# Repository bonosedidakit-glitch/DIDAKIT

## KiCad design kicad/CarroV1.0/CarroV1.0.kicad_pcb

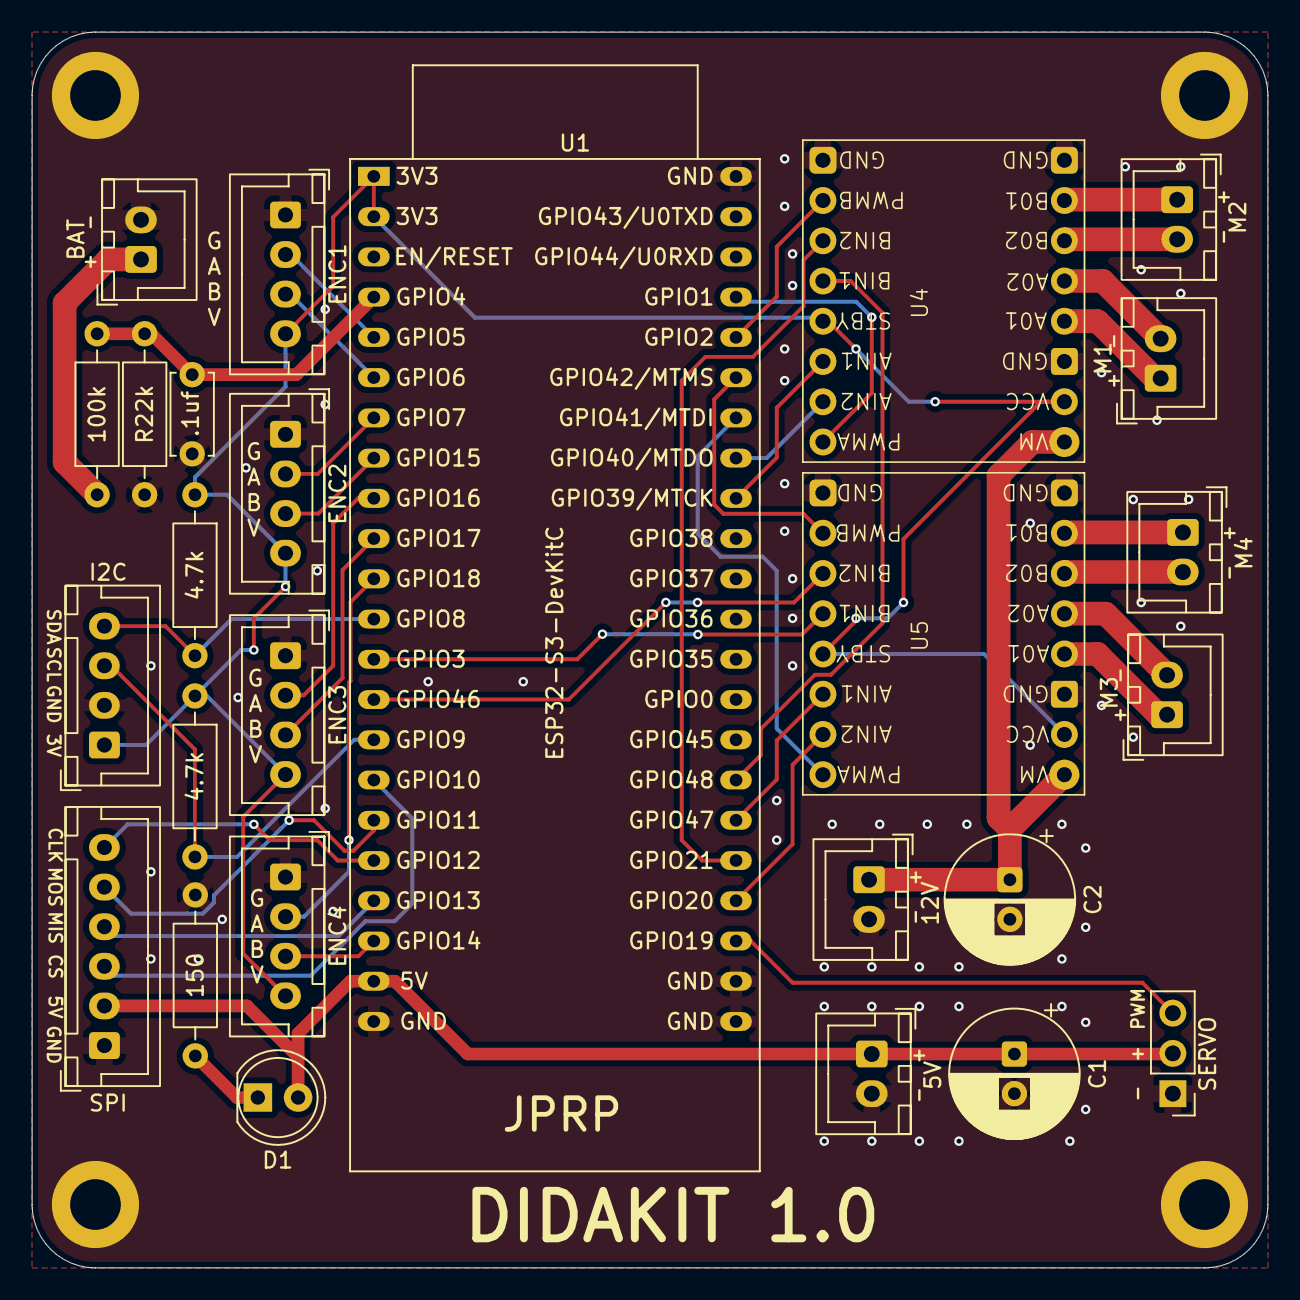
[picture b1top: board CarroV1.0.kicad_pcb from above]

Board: 2 copper layers, 78.0 x 78.0 mm, 26 parts (0 on the bottom side), 42 nets.

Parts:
4.7k: 4.7K; R_Axial_DIN0207_L6.3mm_D2.5mm_P10.16mm_Horizontal
4.7k#2: 4.7k; R_Axial_DIN0207_L6.3mm_D2.5mm_P10.16mm_Horizontal
5V: INPUT 5V; JST_XH_B2B-XH-A_1x02_P2.50mm_Vertical
12V: INPUT 12V; JST_XH_B2B-XH-A_1x02_P2.50mm_Vertical
100k: 100k; R_Axial_DIN0207_L6.3mm_D2.5mm_P10.16mm_Horizontal
150: 150; R_Axial_DIN0207_L6.3mm_D2.5mm_P10.16mm_Horizontal
.1uf: 100nF; C_Disc_D5.0mm_W2.5mm_P5.00mm
BAT: INPUT_battery; JST_XH_B2B-XH-A_1x02_P2.50mm_Vertical
C1, C2: 1000uF; CP_Radial_D8.0mm_P2.50mm
D1: LED; LED_D5.0mm
ENC1, ENC2, ENC3, ENC4: JST_XH_B4B-XH-A_1x04_P2.50mm_Vertical
I2C: JST_XH_B4B-XH-A_1x04_P2.50mm_Vertical
M1, M2, M3, M4: JST_XH_B2B-XH-A_1x02_P2.50mm_Vertical
R22k: 22k; R_Axial_DIN0207_L6.3mm_D2.5mm_P10.16mm_Horizontal
SERVO: Motor_Servo; PinHeader_1x03_P2.54mm_Vertical
SPI: JST_XH_B6B-XH-A_1x06_P2.50mm_Vertical
U1: ESP32-S3-DevKitC
U4, U5: TB6612FNG

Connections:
3.3v: 4.7k.1, 4.7k#2.1, ENC1.4 (VCC), ENC2.4 (VCC), ENC3.4 (VCC), ENC4.4 (VCC), I2C.1 (VCC), U1.1 (3V3), U1.2 (3V3), U4.2 (VCC), U4.12 (STBY), U5.2 (VCC), U5.12 (STBY)
5v: 5V.1, C1.1, D1.2 (A), SERVO.2 (+), SPI.2 (5V), U1.21 (5V)
12v: 12V.1, C2.1, U4.1 (VM), U5.1 (VM)
BAT: 100k.2, .1uf.2, R22k.2, U1.4 (GPIO4/ADC1_CH3)
DIRM11: U1.36 (GPIO39/MTCK), U4.11 (AIN1)
DIRM12: U1.37 (GPIO40/MTDO), U4.10 (AIN2)
DIRM21: U1.29 (GPIO48), U4.13 (BIN1)
DIRM22: U1.27 (GPIO21), U4.14 (BIN2)
DIRM31: U1.28 (GPIO47), U5.11 (AIN1)
DIRM32: U1.26 (GPIO20/USB_D+), U5.10 (AIN2)
DIRM41: U1.13 (GPIO3/ADC1_CH2), U5.13 (BIN1)
DIRM42: U1.14 (GPIO46), U5.14 (BIN2)
GND: 5V.2, 12V.2, 150.1, .1uf.1, BAT.2, C1.2, C2.2, ENC1.1 (GND), ENC2.1 (GND), ENC3.1 (GND), ENC4.1 (GND), I2C.2 (GND), R22k.1, SERVO.1 (PWM), SPI.1 (GND), U1.22 (GND), U1.23 (GND), U1.24 (GND), U1.44 (GND), U4.3 (GND), U4.8 (GND), U4.16 (GND), U5.3 (GND), U5.8 (GND), U5.16 (GND)
M1A: ENC1.2 (ENCA), U1.5 (GPIO5/ADC1_CH4)
M1B: ENC1.3 (ENCB), U1.6 (GPIO6/ADC1_CH5)
M2A: ENC2.2 (ENCA), U1.7 (GPIO7/ADC1_CH6)
M2B: ENC2.3 (ENCB), U1.8 (GPIO15/ADC2_CH4/32K_P)
M3A: ENC3.2 (ENCA), U1.9 (GPIO16/ADC2_CH5/32K_N)
M3B: ENC3.3 (ENCB), U1.10 (GPIO17/ADC2_CH6)
M4A: ENC4.2 (ENCA), U1.11 (GPIO18/ADC2_CH7)
M4B: ENC4.3 (ENCB), U1.20 (GPIO14/ADC2_CH3)
MISO: SPI.4 (MISO), U1.19 (GPIO13/ADC2_CH2)
MOSI: SPI.5 (MOSI), U1.17 (GPIO11/ADC2_CH0)
NCS: SPI.3 (NCS), U1.16 (GPIO10/ADC1_CH9)
unnamed: 150.2, D1.1 (K)
PWMM1: U1.41 (GPIO1/ADC1_CH0), U4.9 (PWMA)
PWMM2: U1.40 (GPIO2/ADC1_CH1), U4.15 (PWMB)
PWMM3: U1.38 (GPIO41/MTDI), U5.9 (PWMA)
PWMM4: U1.39 (GPIO42/MTMS), U5.15 (PWMB)
SCL: 4.7k#2.2, I2C.3 (SCL), U1.15 (GPIO9/ADC1_CH8)
SCLK: SPI.6 (SCLK), U1.18 (GPIO12/ADC2_CH1)
SDA: 4.7k.2, I2C.4 (SDA), U1.12 (GPIO8/ADC1_CH7)
SVM: SERVO.3 (-), U1.25 (GPIO19/USB_D-)
VM1+: M1.1 (V+), U4.4 (A01)
VM1-: M1.2 (V-), U4.5 (A02)
VM2+: M2.1 (V+), U4.7 (B01)
VM2-: M2.2 (V-), U4.6 (B02)
VM3+: M3.1 (V+), U5.4 (A01)
VM3-: M3.2 (V-), U5.5 (A02)
VM4+: M4.1 (V+), U5.7 (B01)
VM4-: M4.2 (V-), U5.6 (B02)
V_BAT+: 100k.1, BAT.1
